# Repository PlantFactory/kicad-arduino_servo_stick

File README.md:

# kicad-arduino_servo_stick
The board implements translator arduino to joy stick (#27800).

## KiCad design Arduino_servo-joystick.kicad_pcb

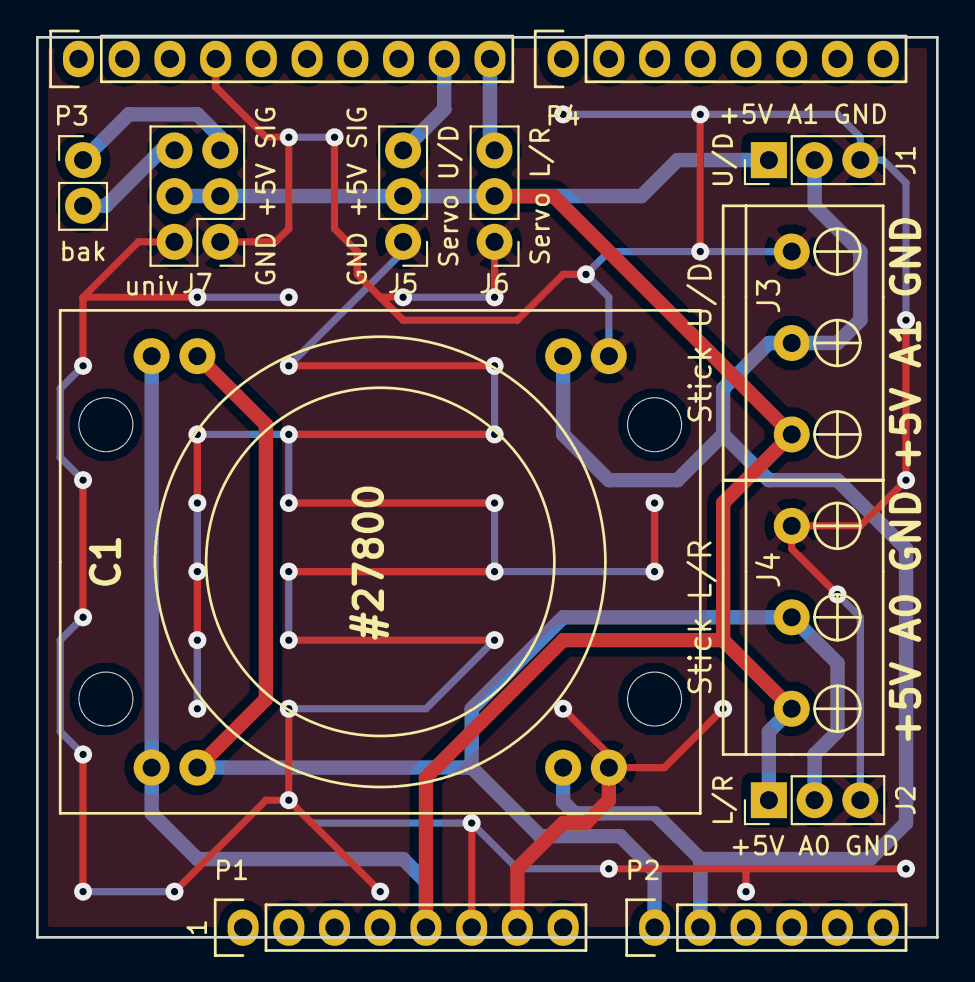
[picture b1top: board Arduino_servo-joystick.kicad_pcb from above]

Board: 2 copper layers, 50.0 x 50.0 mm, 13 parts (0 on the bottom side), 8 nets.

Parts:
C1: #27800; 27800
J1: U/D; Pin_Header_Straight_1x03_Pitch2.54mm
J2: L/R; Pin_Header_Straight_1x03_Pitch2.54mm
J3: Stick U/D; TerminalBlock3
J4: Stick L/R; TerminalBlock3
J5: Servo U/D; Pin_Header_Straight_1x03_Pitch2.54mm
J6: Servo L/R; Pin_Header_Straight_1x03_Pitch2.54mm
J7: univ; Pin_Header_Straight_2x03_Pitch2.54mm
P1: Power; Socket_Strip_Arduino_1x08
P2: Analog; Socket_Strip_Arduino_1x06
P3: Digital; Socket_Strip_Arduino_1x10
P4: Digital; Socket_Strip_Arduino_1x08
bak: Pin_Header_Straight_1x02_Pitch2.54mm

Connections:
+5V: C1.1, C1.5, J1.1, J2.1, J3.1, J4.1, J5.2, J6.2, J7.3, J7.4, P1.5
/8: J6.3, P3.10
/9(**): J5.3, P3.9
/A0: C1.2, C1.6, J2.2, J4.2, P2.1
/A1: C1.3, C1.7, J1.2, J3.2, P2.2
GND: C1.4, C1.8, J1.3, J2.3, J3.3, J4.3, J5.1, J6.1, J7.1, J7.2, P1.6, P1.7, P3.4
unnamed: J7.5, bak.1
unnamed: J7.6, bak.2
